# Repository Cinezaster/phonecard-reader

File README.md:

# Phonecard-reader

A phonecard reader that outputs the memory of a phonecard in hexadecimal via keystrokes

## Requirements

- should read the memory of Gen 1 phonecards
- should read the memory of Gen 2 ISO 7816 phonecards
- should return the memory as a hex string to a computer or smartphone as keystrokes
- should check if memory can be read consistently

## Specs

- a 16pin card reader for iso 7816 and AFNOR type of cards: [RS-online](https://befr.rs-online.com/web/p/memory-card-connectors/0252585/)
- a 5V MCU with HID capacity like [arduino micro](https://store.arduino.cc/arduino-micro) or [Adafruit ItsyBitsy 32u4 5V](https://www.adafruit.com/product/3677)

## Hardware

A 1-Layer smd pcb.

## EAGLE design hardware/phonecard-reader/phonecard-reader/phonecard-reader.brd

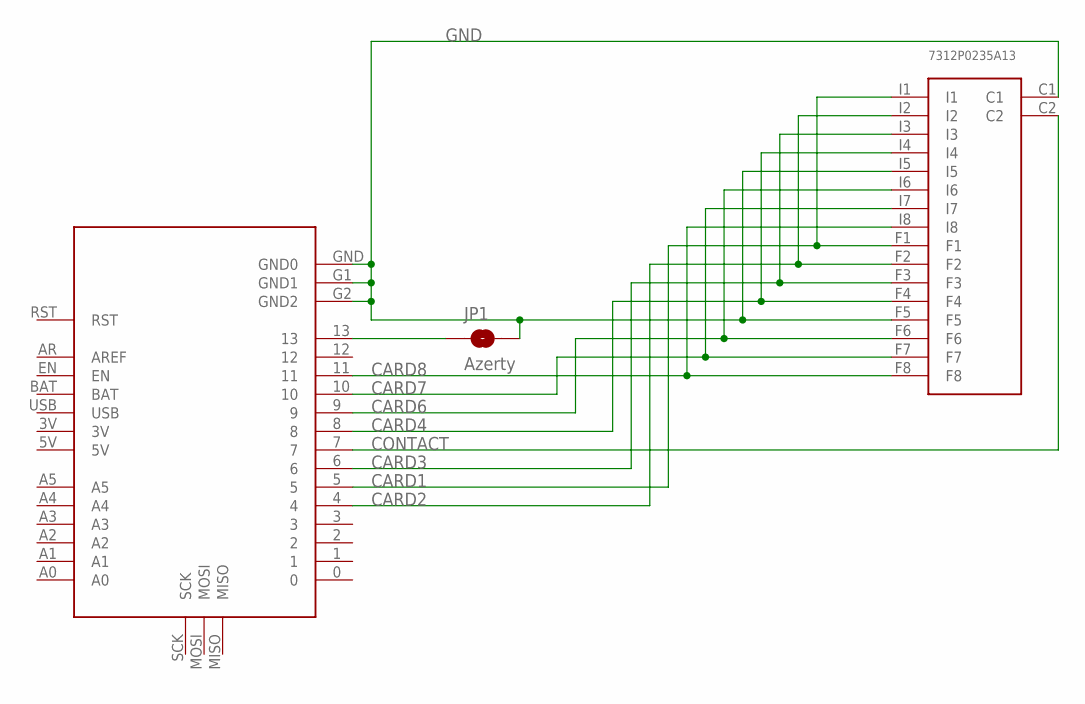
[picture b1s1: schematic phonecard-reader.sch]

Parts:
JP1: Azerty; SMT-JUMPER_2_NO_SILK_ROUND
U$1: Itsy Bitsy 5V; ITSY_BITSY_SMD
U$2: 7312P0235A13LFC; 7312P0235A13

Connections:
CARD1: U$1.5, U$2.F1, U$2.I1
CARD2: U$1.4, U$2.F2, U$2.I2
CARD3: U$1.6, U$2.F3, U$2.I3
CARD4: U$1.8, U$2.F4, U$2.I4
CARD6: U$1.9, U$2.F6, U$2.I6
CARD7: U$1.10, U$2.F7, U$2.I7
CARD8: U$1.11, U$2.F8, U$2.I8
CONTACT: U$1.7, U$2.C2
GND: JP1.2, U$1.G1 (GND1), U$1.G2 (GND2), U$1.GND (GND0), U$2.C1, U$2.F5, U$2.I5
unnamed: JP1.1, U$1.13

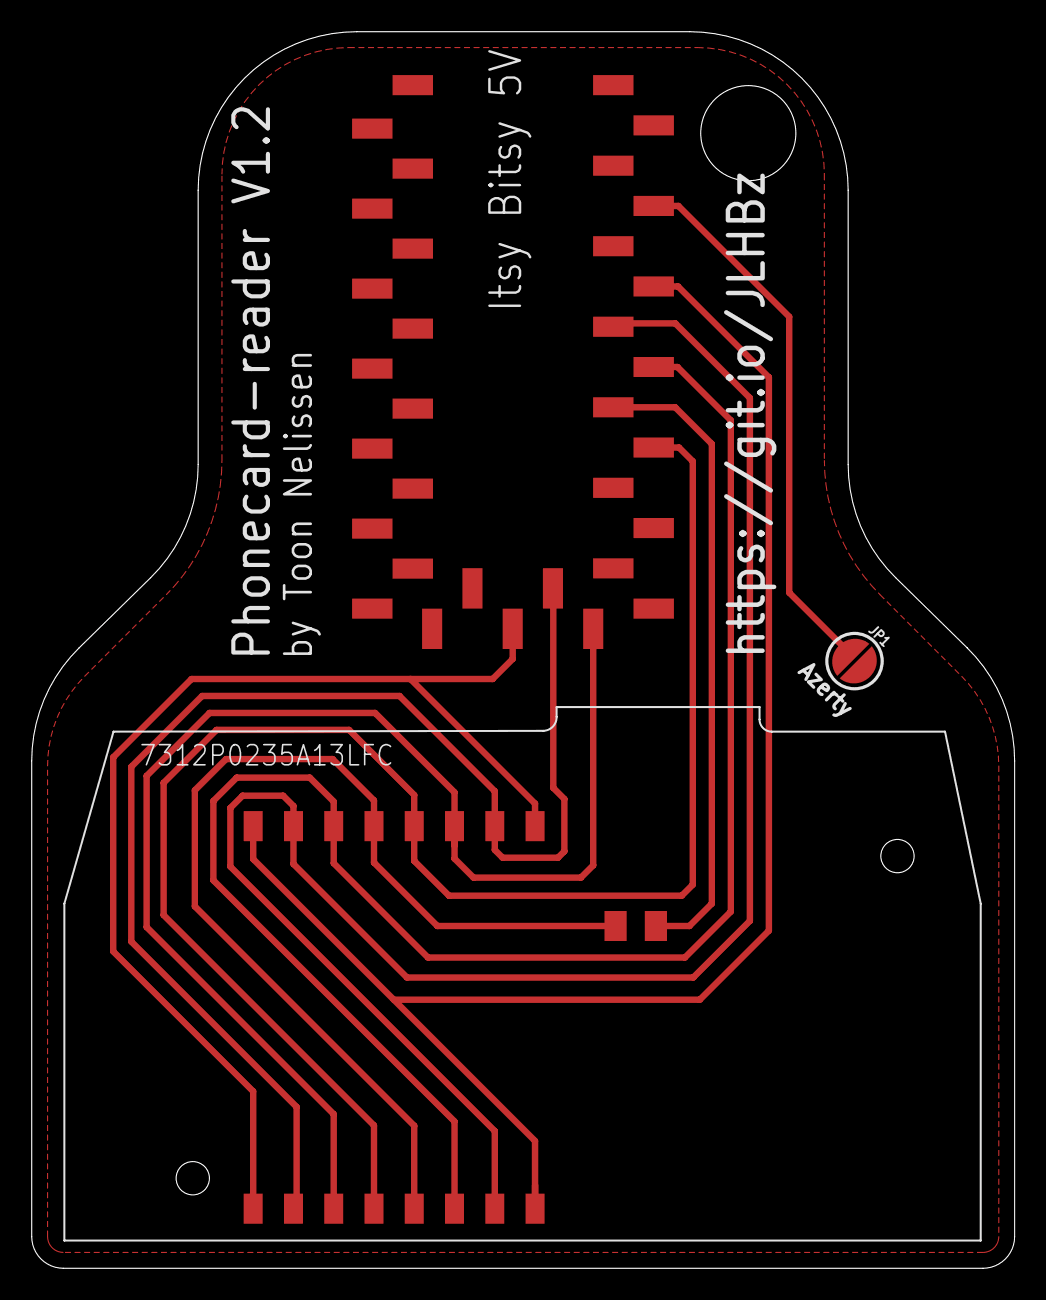
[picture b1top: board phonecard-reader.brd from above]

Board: 2 copper layers, 62.0 x 78.0 mm, 3 parts (0 on the bottom side), 10 nets.

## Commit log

2020-12-11 feat: firmware
2020-12-30 docs: add card footprints
2020-12-30 feat: keyboard read + checks
2020-12-30 feat: add hardware schematics and board
2020-12-30 fix: image url
2020-12-30 feat: add hardware media
2020-12-30 feat: added azerty keyboard output jumper to pcb
2020-12-31 feat: update keyboard switch pin
2020-12-31 feat: images

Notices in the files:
parts and their libraries:
SparkFun-Jumpers: Licensing: Creative Commons ShareAlike 4.0 International - https://creativecommons.org/licenses/by-sa/4.0
